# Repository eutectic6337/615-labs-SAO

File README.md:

# 615-labs-SAO
Science of debatable sanity

- 35mm x 50mm
- 4x green back-emitting SMD LEDs, rear mounted, glow through bare PCB spot
- microcontroller inc programming pads
- dropper resistors
- SAO connector, rear mounted
- dithered green soldermask, with white silkscreen?

## process
- KiCad
  - create project
  - create schematic
    - place simple devices: (1x) LED, R, C
      rough calculation: *if* LED forward voltage drop is (typical) 1.6V, resistor needs to drop 3.3V-1.6V = 1.7V
      *if* LED forward current is (typical) 20mA, V=IR ... 1.7 = 20e-3 x R ... R=85
      but LEDs produce more light per watt at higher currents, and we can PWM it down arbitrarily, so drop Rto about 20
      E12 series: 22

- place SAO connector and CPU on schematic, wire together

- browse [JLCPCB's assembly parts library](https://jlcpcb.com/parts)
  - Optoelectronic / LED Discrete
    - checkboxes: In-stock, Economic PCBA, Datasheet available
    - filters: color (control-click each variant containing "Green" and no comma), mounting Reverse
    - checkbox Parts Type Basic not even selectable (because reverse-emitting)
    - Apply
    - sort by price ascending
      - [cheapest](https://jlcpcb.com/partdetail/C7496852) at 1.14 cents in qty 1, and they have 3k in stock
      - [second cheapest](https://jlcpcb.com/partdetail/XINGLIGHT-XL_3216UGCFB/C3646937) at 1.42 cents in qty 1, and they have over 700k in stock
        but its forward voltage Vf might possibly sneak over 3.3V so it's not a viable option; back to the cheaper one
    - Add to My Part Lib for Assembly
    - grab datasheet
    - forward voltage drop Vf is 2.4 .. 2.7 - current thus 0.6/22 .. 0.9/22 = 27 .. 41 mA - almost inside absolute max pulse current - fuck it we ride
    - make new schematic symbol and PCB footprint based off existing LED and 1206

  - Resistors / Chip surface mount
    - checkboxes: In-stock, Basic, Economic PCBA, (don't care about Datasheet here)
    - filters: resistance: 21 to 23 ohm - select 22
    - Apply
    - sort by price ascending
      - [cheapest](https://jlcpcb.com/partdetail/25835-0402WGF220JTCE/C25092) at 0.07 cents in qty 1
    - Add to My Part Lib for Assembly
    - package is 0402 - update schematic and thus PCB

  - Connectors / Pin headers
    - use same as already selected for doom-floppy-SAO

  - Capacitors / Multi-Layer Ceramic SMD
    - checkboxes: In-stock, Basic, Economic PCBA, (don't care about Datasheet here)
    - filters: capacitance: 1 to 10 uF - browse through
    - Apply
    - sort by price ascending
      - [choice - highest value under 1c each](https://jlcpcb.com/partdetail/24366-CL10A225KO8NNNC/C23630) at 0.83 cents in qty 1
    - Add to My Part Lib for Assembly
    - package is 0603 - update schematic and thus PCB

- on layer Edge Cuts, place rectangle; edit, start point 50,50; size 35x50

- in schematic
  - make 7 copies of R and LED
  - for each GPIO pin, right-click and select function - if there's a TIMn_CHm, select it (that's PWM outputs, primary pin assignment)
  - one pin has function SWIO - select it and wire to SAO GPIO1 pin - program by connecting WCH-LinkE to SAO connector
  - wire from each TIMnCHm to one R and thus through LED to GND (doesn't matter which - will reallocate based on board routing)

- from schematic, Tools / Update PCB

- as-built GPIO-LED assignments:
  - LED1 - Timer 2 Ch 4 / aka PD7
  - LED2 - Timer 2 Ch 1 / aka PD4
  - LED3 - Timer 1 Ch 2 / aka PA1
  - LED4 - Timer 2 Ch 2 / aka PD3
  - LED5 - Timer 1 Ch 4 / aka PC4
  - LED6 - Timer 1 Ch 1 / aka PD2
  - LED7 - Timer 1 Ch 3 / aka PC3
  - LED8 - Timer 2 Ch 3 / aka PC0

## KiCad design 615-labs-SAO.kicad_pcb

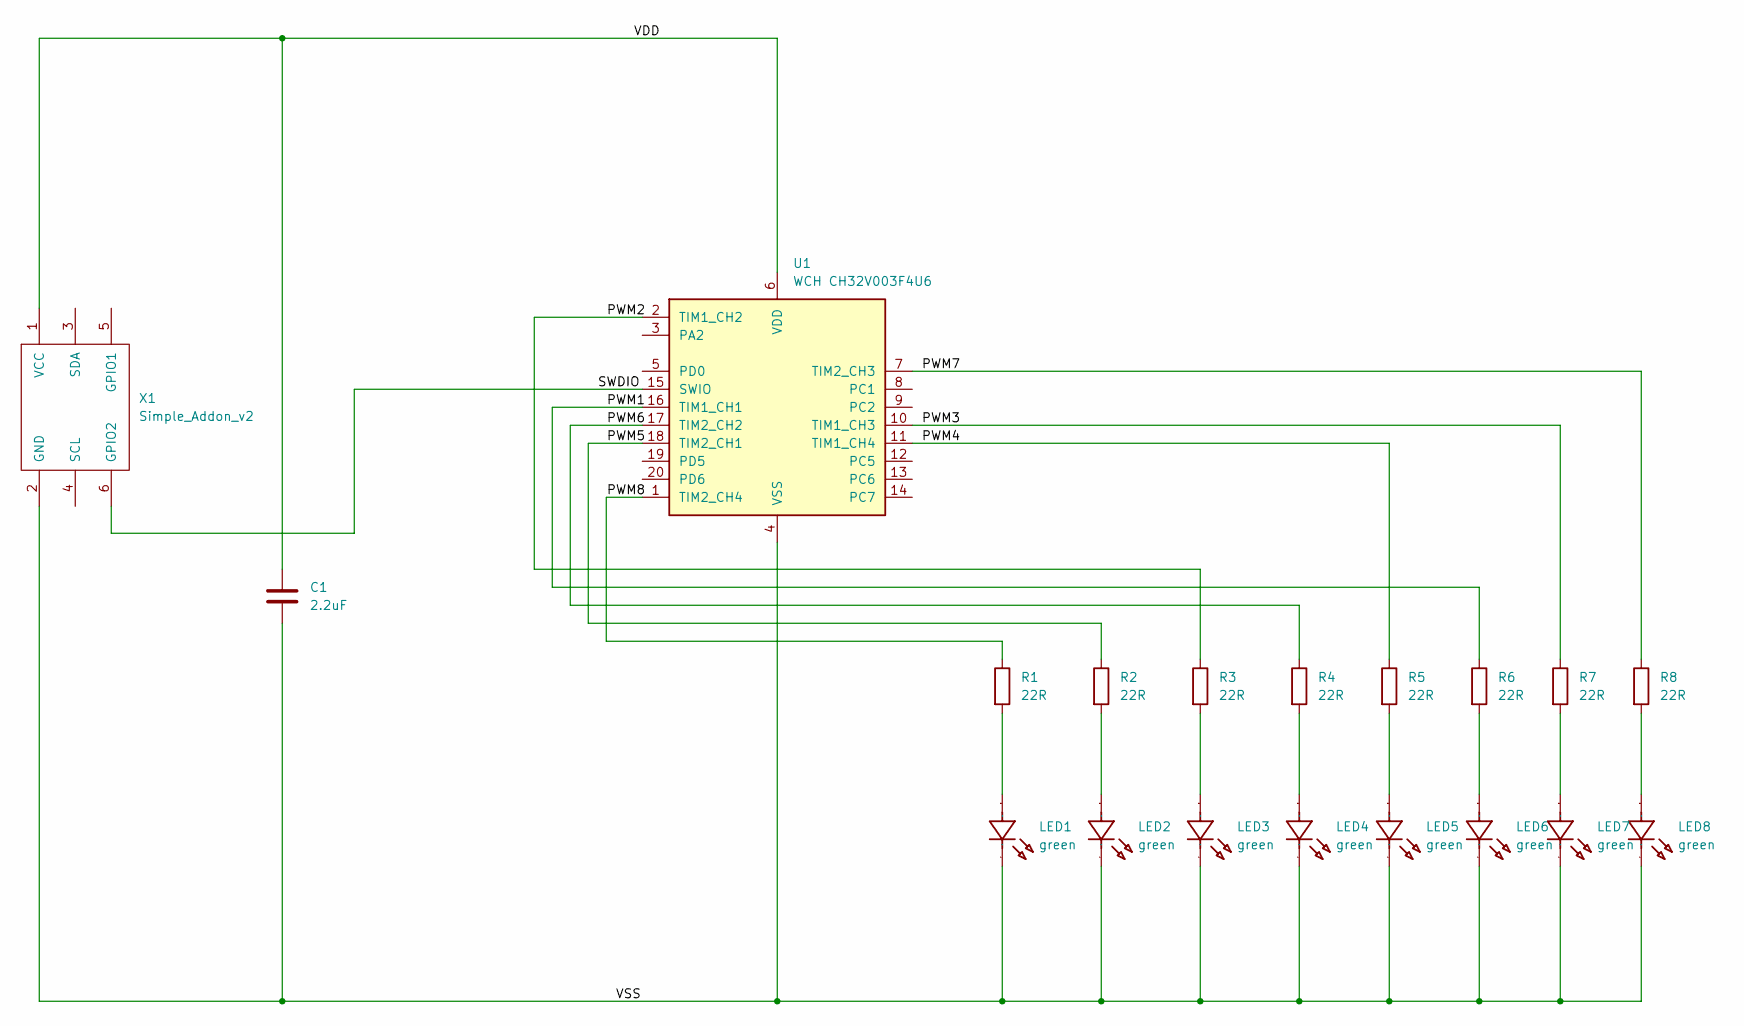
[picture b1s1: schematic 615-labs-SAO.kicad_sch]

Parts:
C1: 2.2uF; C_0603_1608Metric
LED1, LED2, LED3, LED4, LED5, LED6, LED7, LED8: green; LED1206-FD_GREEN-EH; Manufacturer Part XL-3216UGC-FB; LCSC Part Name 1206翠绿（反编）贴片式发光二极管
R1, R2, R3, R4, R5, R6, R7, R8: 22R; R_0402_1005Metric
U1: WCH CH32V003F4U6; QFN-20-1EP_3x3mm_P0.4mm_EP1.65x1.65mm_ThermalVias
X1: Simple_Addon_v2; IDC-Header_2x03_P2.54mm_Vertical_SMD

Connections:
/PWM1: R6.1, U1.16 (TIM1_CH1)
/PWM2: R3.1, U1.2 (TIM1_CH2)
/PWM3: R7.1, U1.10 (TIM1_CH3)
/PWM4: R5.1, U1.11 (TIM1_CH4)
/PWM5: R2.1, U1.18 (TIM2_CH1)
/PWM6: R4.1, U1.17 (TIM2_CH2)
/PWM7: R8.1, U1.7 (TIM2_CH3)
/PWM8: R1.1, U1.1 (TIM2_CH4)
/SWDIO: U1.15 (SWIO), X1.6 (GPIO2)
/VDD: C1.1, U1.6 (VDD), X1.1 (VCC)
unnamed: LED1.1 (A), R1.2
unnamed: LED2.1 (A), R2.2
unnamed: LED3.1 (A), R3.2
unnamed: LED4.1 (A), R4.2
unnamed: LED5.1 (A), R5.2
unnamed: LED6.1 (A), R6.2
unnamed: LED7.1 (A), R7.2
unnamed: LED8.1 (A), R8.2
VSS: C1.2, LED1.2 (K), LED2.2 (K), LED3.2 (K), LED4.2 (K), LED5.2 (K), LED6.2 (K), LED7.2 (K), LED8.2 (K), U1.4 (VSS), U1.21 (VSS), X1.2 (GND)

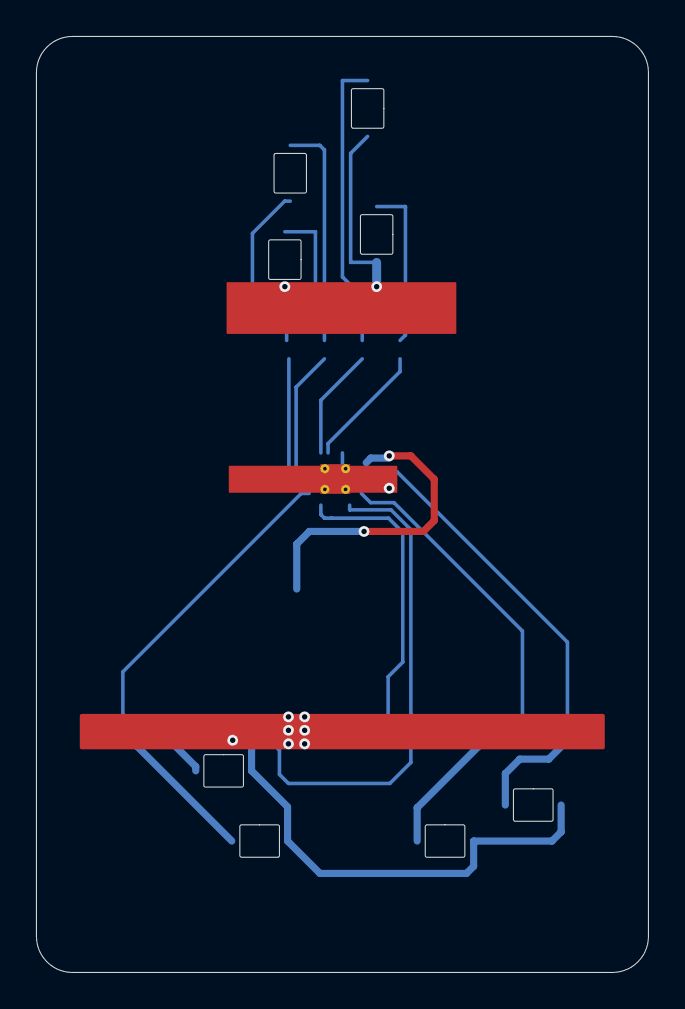
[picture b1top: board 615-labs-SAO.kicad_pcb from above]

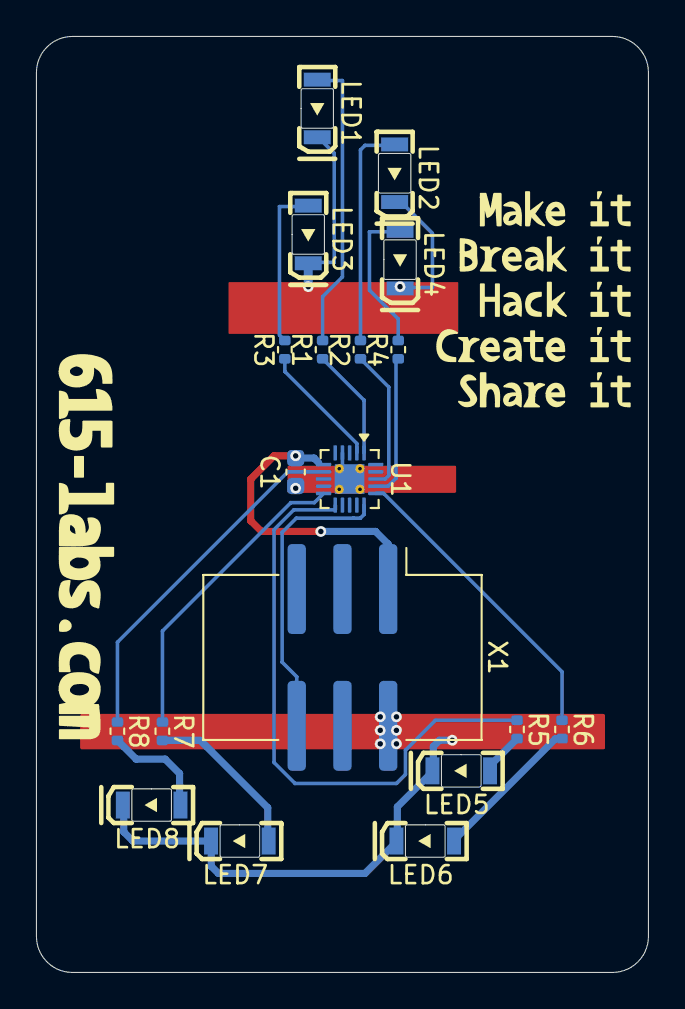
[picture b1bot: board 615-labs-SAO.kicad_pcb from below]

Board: 2 copper layers, 34.0 x 52.0 mm, 19 parts (19 on the bottom side), 19 nets.

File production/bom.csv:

Designator,Footprint,Quantity,Value,LCSC Part #
C1,0603,1,2.2uF,
"LED1, LED2, LED3, LED4, LED5, LED6, LED7, LED8",LED1206-FD_GREEN-EH,8,green,
"R1, R2, R3, R4, R5, R6, R7, R8",0402,8,22R,
U1,QFN-20-1EP_3x3mm_P0.4mm_EP1.65x1.65mm_ThermalVias,1,WCH CH32V003F4U6,
X1,IDC-Header_2x03_P2.54mm_Vertical_SMD,1,Simple_Addon_v2,

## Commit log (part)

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2026-05-30 notes
2026-05-31 start schematic and PCB, and document
2026-05-31 Add initial SVG Layers section to readme
2026-06-01 Add notes on SAO footprint to readme
    Added notes regarding the footprint for the existing surface mount SAO.
2026-06-03 Refactor notes section in artwork/readme.md
    Removed redundant notes section and adjusted formatting.
2026-06-12 got QFN footprint, placed art
2026-06-21 generated fab files
2026-06-21 rounded the corners
2026-06-28 correct SAO connector footprint
2026-06-30 use EasyEDA footprint for reverse-mount LED
